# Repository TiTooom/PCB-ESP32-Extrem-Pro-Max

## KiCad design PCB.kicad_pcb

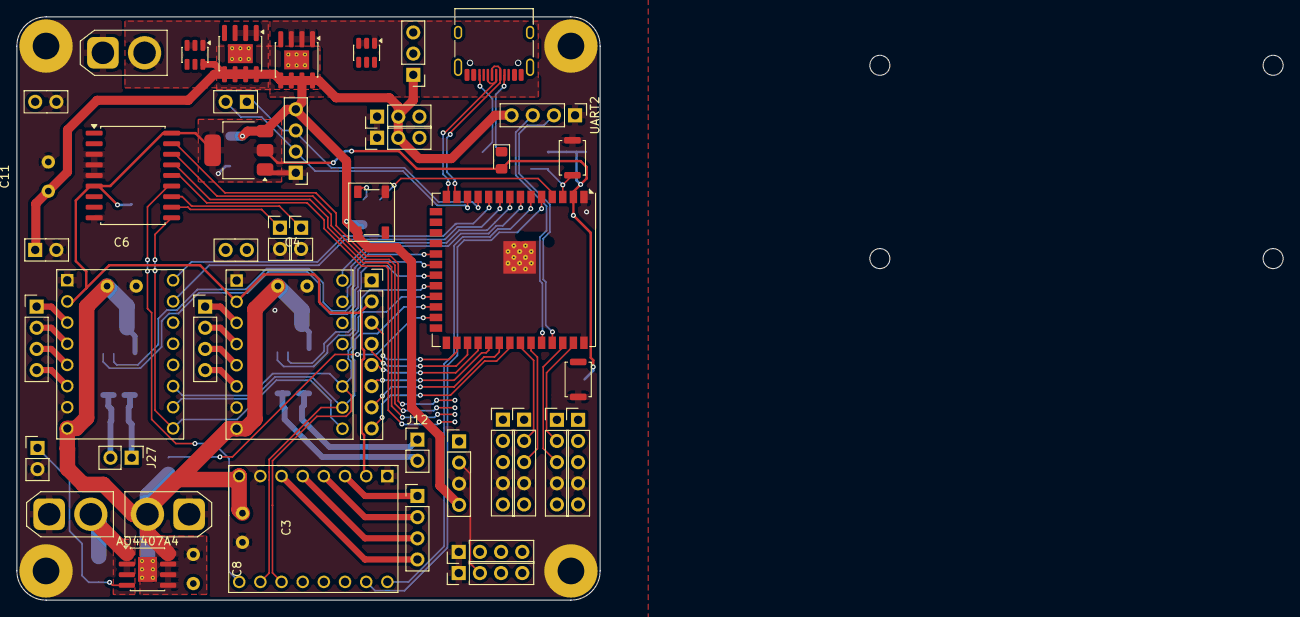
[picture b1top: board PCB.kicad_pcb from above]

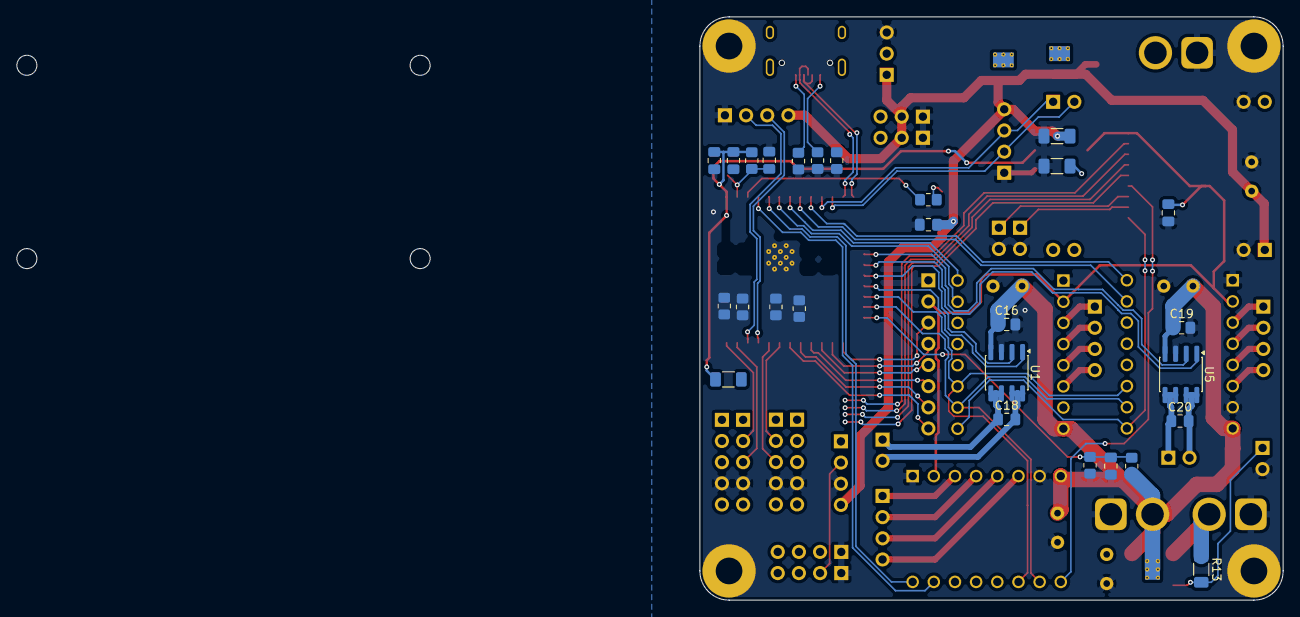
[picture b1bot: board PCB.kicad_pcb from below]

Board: 2 copper layers, 70.0 x 70.0 mm, 78 parts (27 on the bottom side), 74 nets.

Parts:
AO4407A1, AO4407A2, AO4407A4: PMOS; SOIC-8-1EP_3.9x4.9mm_P1.27mm_EP2.29x3mm_ThermalVias
AS1, AS2: Conn_01x04_Pin; PinHeader_1x04_P2.54mm_Vertical
C2: 1uF; C_0805_2012Metric_Pad1.18x1.45mm_HandSolder
C3, C4, C6: 100u; C_Radial_D8.0mm_H11.5mm_P3.50mm
C5, C7: 10uF; C_1206_3216Metric_Pad1.33x1.80mm_HandSolder
C8, C11: 470u; C_Radial_D8.0mm_H11.5mm_P3.50mm
C9: 10uF; C_0805_2012Metric_Pad1.18x1.45mm_HandSolder
C10: 0.1uF; C_0805_2012Metric_Pad1.18x1.45mm_HandSolder
C12, C13, C16, C17, C18, C19, C20: 100nF; C_0805_2012Metric_Pad1.18x1.45mm_HandSolder
D1: LED_0805_2012Metric_Pad1.15x1.40mm_HandSolder
D6: WS2812B; LED_WS2812B_PLCC4_5.0x5.0mm_P3.2mm
H1, H2, H3, H4: MountingHole_Pad; MountingHole_3.2mm_M3_Pad
J1: USB_C_Receptacle_USB2.0_16P; USB_C_Receptacle_HRO_TYPE-C-31-M-12
J2, J4: Conn_01x11_Socket; PinSocket_1x11_P2.54mm_Vertical
J3: Conn_01x08_Socket; PinSocket_1x08_P2.54mm_Vertical
J5, J7, J9, J12, J27: Conn_01x02_Pin; PinHeader_1x02_P2.54mm_Vertical
J6, J10, J15: Conn_01x02_Pin; AMASS_XT30U-F_1x02_P5.0mm_Vertical
J8, J23, J26: Conn_01x03_Pin; PinHeader_1x03_P2.54mm_Vertical
J11, J16, J21: Conn_01x05_Pin; PinHeader_1x05_P2.54mm_Vertical
J13, J14, J22: Conn_01x04_Pin; PinHeader_1x04_P2.54mm_Vertical
MPU1: Conn_01x04_Pin; PinHeader_1x04_P2.54mm_Vertical
R1: 10k; R_0805_2012Metric_Pad1.20x1.40mm_HandSolder
R2, R3: 5.1k; R_0805_2012Metric_Pad1.20x1.40mm_HandSolder
R4: 330; R_0805_2012Metric_Pad1.20x1.40mm_HandSolder
R5, R6, R7, R8: 4.7k; R_0805_2012Metric_Pad1.20x1.40mm_HandSolder
R10, R13: 10k; R_1206_3216Metric_Pad1.30x1.75mm_HandSolder
R12: 470; R_0805_2012Metric_Pad1.20x1.40mm_HandSolder
R14: 180k; R_0805_2012Metric_Pad1.20x1.40mm_HandSolder
R15: 33k; R_0805_2012Metric_Pad1.20x1.40mm_HandSolder
SW1, SW2: SW_Push; SW_Push_SPST_NO_Alps_SKRK
U1, U5: SOIC-8_3.9x4.9mm_P1.27mm
U2, U3: LTC4412xS6; TSOT-23-6
U4: AMS1117-3.3 (UMW); SOT-223-3_TabPin2
U6: ESP32-S3-WROOM-1; ESP32-S3-WROOM-1U
U7, U8, U9: TMC2209_SILENTSTEPSTICK; MODULE_TMC2209_SILENTSTEPSTICK
U10: MCP23008-xSO; SOIC-18W_7.5x11.6mm_P1.27mm
UART1, UART2: Conn_01x04_Pin; PinHeader_1x04_P2.54mm_Vertical
VL0: Conn_01x05_Pin; PinHeader_1x05_P2.54mm_Vertical

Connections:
3V3: C7.1, C9.1, C10.1, C17.1, D1.2 (A), J3.2, R1.1, R5.1, R6.1, R7.1, R8.1, R10.1, U4.2 (VO), U6.2 (3V3), U7.2 (VIO), U8.2 (VIO), U9.2 (VIO), U10.6 (~RESET), U10.18 (VDD)
BAU+: AO4407A4.4 (G), J9.1, R13.2
BLK: J3.8, U6.33 (IO40)
BOOT: R10.2, SW1.2, U6.27 (IO0)
CS: J3.7, U6.32 (IO39)
DC: J3.6, U6.31 (IO38)
DIR1: U6.6 (IO6), U7.9 (DIR)
DIR2: U6.8 (IO15), U8.9 (DIR)
DIR3: U6.10 (IO17), U9.9 (DIR)
EN1: U8.16 (~EN), U9.16 (~EN), U10.10 (GP0)
EN2: U7.16 (~EN), U10.13 (GP3)
ESP32_EN: C2.1, R1.2, SW2.2, U6.3 (EN)
GND: AS1.1, AS2.1, C2.2, C3.2, C4.2, C5.2, C6.2, C7.2, C8.2, C9.2, C10.2, C11.2, C12.2, C13.2, C16.2, C17.2, C19.2, D6.3 (VSS), H1.1 (1_1), H2.1 (1_1), H3.1 (1_1), H4.1 (1_1), J1.A1 (GND), J1.A12 (GND), J1.B1 (GND), J1.B12 (GND), J2.10, J3.1, J4.2, J5.2, J6.1, J7.2, J8.3, J9.2, J10.1, J11.4, J15.1, J16.4, J21.4, J23.1, J26.1, MPU1.3, R2.2, R3.2, R4.2, R15.1, SW1.1, SW2.1, U1.3 (GND), U2.2 (GND), U2.3 (CTL), U3.2 (GND), U3.3 (CTL), U4.1 (GND), U5.3 (GND), U6.1 (GND), U6.40 (GND), U6.41 (GND), U7.1 (GND), U7.7 (GND), U8.1 (GND), U8.7 (GND), U9.1 (GND), U9.7 (GND), U10.3 (A2), U10.4 (A1), U10.5 (A0), U10.9 (VSS), UART1.1, UART2.1, VL0.4
LAUNCHPULL: J7.1, U10.12 (GP2)
M1+: C18.1, J12.1, U1.5 (Fo), U1.6 (Fo)
M1-: C18.2, J12.2, U1.7 (Bo), U1.8 (Bo)
M1_IN1: U1.2 (FI), U6.21 (IO13)
M1_IN2: U1.1 (BI), U6.22 (IO14)
M2+: C20.1, J27.1, U5.5 (Fo), U5.6 (Fo)
M2-: C20.2, J27.2, U5.7 (Bo), U5.8 (Bo)
M2_IN1: U5.2 (FI), U6.19 (IO11)
M2_IN2: U5.1 (BI), U6.20 (IO12)
MOSI: J3.4, U6.29 (IO36)
MOTORA1: J13.1, U7.3 (M1B)
MOTORA2: J13.2, U7.4 (M1A)
MOTORA3: J13.3, U7.5 (M2A)
MOTORA4: J13.4, U7.6 (M2B)
MOTORB1: J14.1, U8.3 (M1B)
MOTORB2: J14.2, U8.4 (M1A)
MOTORB3: J14.3, U8.5 (M2A)
MOTORB4: J14.4, U8.6 (M2B)
MOTORC1: J22.1, U9.3 (M1B)
MOTORC2: J22.2, U9.4 (M1A)
MOTORC3: J22.3, U9.5 (M2A)
MOTORC4: J22.4, U9.6 (M2B)
MS1: U6.24 (IO47), U7.15 (MS1), U8.15 (MS1), U9.15 (MS1)
MS2: U6.23 (IO21), U7.14 (MS2), U8.14 (MS2), U9.14 (MS2)
NEOPIXEL: R12.1, U6.4 (IO4)
NEOPIXEL+: D6.2 (DOUT), J8.2
unnamed: AO4407A1.4 (G), U2.5 (GATE)
unnamed: AO4407A2.4 (G), U3.5 (GATE)
unnamed: D1.1 (K), R4.1
unnamed: D6.4 (DIN), R12.2
unnamed: J1.A5 (CC1), R3.1
unnamed: J1.B5 (CC2), R2.1
RST: J3.5, U6.30 (IO37)
SCL1: AS1.2, J16.3, J21.3, R5.2, U6.38 (IO2), U10.1 (SCL)
SCL2: AS2.2, J11.3, MPU1.2, R7.2, U6.35 (IO42), VL0.3
SCLK: J3.3, U6.28 (IO35)
SDA1: AS1.3, J16.2, J21.2, R6.2, U6.39 (IO1), U10.2 (SDA)
SDA2: AS2.3, J11.2, MPU1.1, R8.2, U6.34 (IO41), VL0.2
SERVO0: J23.3, U6.17 (IO9)
SERVO1: J26.3, U6.18 (IO10)
STEP1: U6.5 (IO5), U7.10 (STEP)
STEP2: U6.7 (IO7), U8.10 (STEP)
STEP3: U6.9 (IO16), U9.10 (STEP)
TEAM_BTN: J5.1, U10.11 (GP1)
UART0_RX-: U6.36 (RXD0), UART2.3
UART0_TX+: U6.37 (TXD0), UART2.2
UART1_RX-: J2.1, U6.11 (IO18), UART1.3
UART1_TX+: J2.2, U6.12 (IO8), UART1.2
USB_N: J1.A7 (D-), J1.B7 (D-), U6.13 (IO19)
USB_P: J1.A6 (D+), J1.B6 (D+), U6.14 (IO20)
VCC_5V_BUCK: AO4407A2.1 (S), AO4407A2.2 (S), AO4407A2.3 (S), J15.2, U3.1 (VIN)
VCC_5V_GLOBAL: AO4407A1.5 (D), AO4407A1.6 (D), AO4407A1.7 (D), AO4407A1.8 (D), AO4407A1.9 (D), AO4407A2.5 (D), AO4407A2.6 (D), AO4407A2.7 (D), AO4407A2.8 (D), AO4407A2.9 (D), AS1.4, AS2.4, C5.1, C11.1, C12.1, D6.1 (VDD), J4.1, J8.1, J11.5, J16.5, J21.5, J23.2, J26.2, MPU1.4, U2.6 (SENSE), U3.6 (SENSE), U4.3 (VI), UART1.4, UART2.4, VL0.5
VCC_5V_USB: AO4407A1.1 (S), AO4407A1.2 (S), AO4407A1.3 (S), U2.1 (VIN)
VCC_5V_USB_IN: J1.A4 (VBUS), J1.A9 (VBUS), J1.B4 (VBUS), J1.B9 (VBUS)
VCC_12V: AO4407A4.5 (D), AO4407A4.6 (D), AO4407A4.7 (D), AO4407A4.8 (D), AO4407A4.9 (D), C3.1, C4.1, C6.1, C8.1, C16.1, C19.1, J10.2, R14.2, U1.4 (VCC), U5.4 (VCC), U7.8 (VM), U8.8 (VM), U9.8 (VM)
VCC_12V_IN: AO4407A4.1 (S), AO4407A4.2 (S), AO4407A4.3 (S), J6.2, R13.1
VCC_CALC: C13.1, R14.1, R15.2, U6.25 (IO48)
XSHUT0: U10.14 (GP4), VL0.1
XSHUT1: J11.1, U10.15 (GP5)
XSHUT2: J16.1, U10.16 (GP6)
XSHUT3: J21.1, U10.17 (GP7)

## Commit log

2026-04-15 ajout driver & retrofit
2026-05-19 ajout nema17, + debut pcb
2026-05-21 ajout vcc calc & mise forme pcb
2026-05-21 fix BAU + bug
2026-05-22 fix BAU
2026-05-25 changement driver + debut root pcb
2026-05-25 debut root pcb
2026-05-26 suite routage
2026-06-07 routage
2026-06-10 suite routage + séparation 2eme pcb avec 2 nema
